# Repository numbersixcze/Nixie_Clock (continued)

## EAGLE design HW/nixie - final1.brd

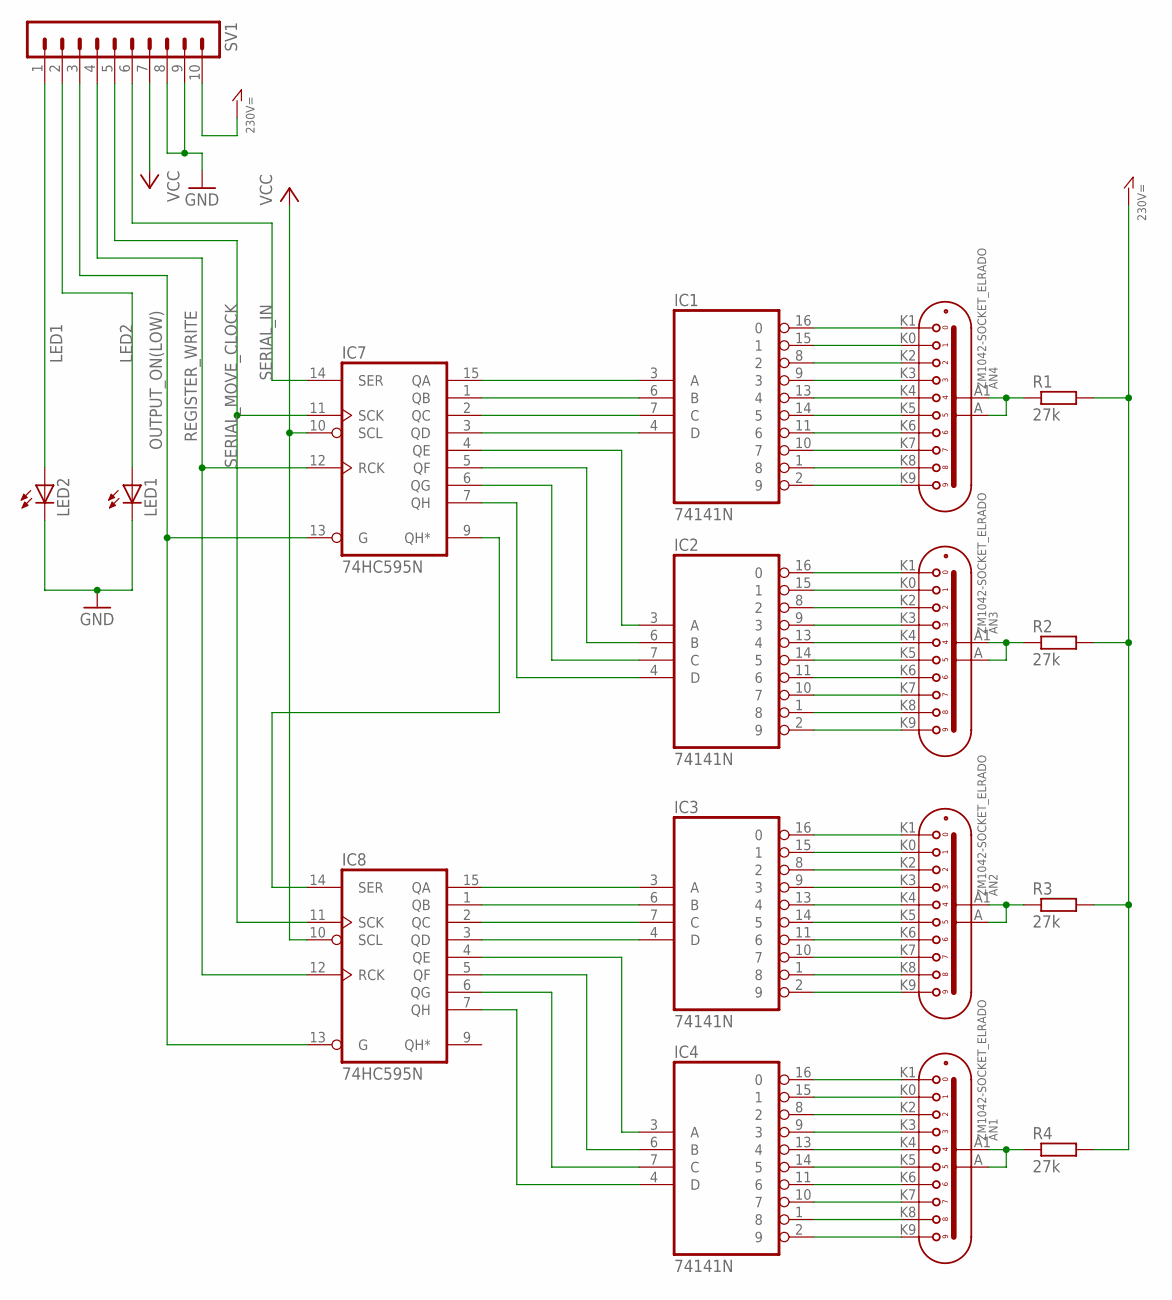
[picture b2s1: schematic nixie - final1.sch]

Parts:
AN1, AN2, AN3, AN4: ZM1042-SOCKET_ELRADO; ZM1040.SOCKET
IC1, IC2, IC3, IC4: 74141N; DIL16
IC7, IC8: 74HC595N; DIL16
LED1, LED2: LED_ELD260; LED_LD260
R1, R2, R3, R4: 27k; 0309/12
SV1: MA10-1

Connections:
230V=: R1.2, R2.2, R3.2, R4.2, SV1.10
GND: IC1.12 (GND), IC2.12 (GND), IC3.12 (GND), IC4.12 (GND), IC7.8 (GND), IC8.8 (GND), LED1.K (C), LED2.K (C), SV1.8, SV1.9
LED1: LED2.A, SV1.1
LED2: LED1.A, SV1.2
unnamed: AN4.K1 (0), IC1.16 (0)
unnamed: AN4.K0 (1), IC1.15 (1)
unnamed: AN4.K2 (2), IC1.8 (2)
unnamed: AN4.K3 (3), IC1.9 (3)
unnamed: AN4.K4 (4), IC1.13 (4)
unnamed: AN4.K5 (5), IC1.14 (5)
unnamed: AN4.K6 (6), IC1.11 (6)
unnamed: AN4.K7 (7), IC1.10 (7)
unnamed: AN4.K8 (8), IC1.1 (8)
unnamed: AN4.K9 (9), IC1.2 (9)
unnamed: AN1.K0 (1), IC4.15 (1)
unnamed: AN1.K2 (2), IC4.8 (2)
unnamed: AN1.K4 (4), IC4.13 (4)
unnamed: AN1.K3 (3), IC4.9 (3)
unnamed: AN1.K5 (5), IC4.14 (5)
unnamed: AN1.K6 (6), IC4.11 (6)
unnamed: AN1.K7 (7), IC4.10 (7)
unnamed: AN1.K8 (8), IC4.1 (8)
unnamed: AN1.K9 (9), IC4.2 (9)
unnamed: AN1.K1 (0), IC4.16 (0)
unnamed: AN2.K0 (1), IC3.15 (1)
unnamed: AN2.K2 (2), IC3.8 (2)
unnamed: AN2.K4 (4), IC3.13 (4)
unnamed: AN2.K3 (3), IC3.9 (3)
unnamed: AN2.K5 (5), IC3.14 (5)
unnamed: AN2.K6 (6), IC3.11 (6)
unnamed: AN2.K7 (7), IC3.10 (7)
unnamed: AN2.K8 (8), IC3.1 (8)
unnamed: AN2.K9 (9), IC3.2 (9)
unnamed: AN2.K1 (0), IC3.16 (0)
unnamed: AN3.K0 (1), IC2.15 (1)
unnamed: AN3.K2 (2), IC2.8 (2)
unnamed: AN3.K4 (4), IC2.13 (4)
unnamed: AN3.K3 (3), IC2.9 (3)
unnamed: AN3.K5 (5), IC2.14 (5)
unnamed: AN3.K6 (6), IC2.11 (6)
unnamed: AN3.K7 (7), IC2.10 (7)
unnamed: AN3.K8 (8), IC2.1 (8)
unnamed: AN3.K9 (9), IC2.2 (9)
unnamed: AN3.K1 (0), IC2.16 (0)
unnamed: IC1.3 (A), IC7.15 (QA)
unnamed: IC1.6 (B), IC7.1 (QB)
unnamed: IC1.7 (C), IC7.2 (QC)
unnamed: IC1.4 (D), IC7.3 (QD)
unnamed: IC2.3 (A), IC7.4 (QE)
unnamed: IC2.6 (B), IC7.5 (QF)
unnamed: IC2.7 (C), IC7.6 (QG)
unnamed: IC2.4 (D), IC7.7 (QH)
unnamed: IC3.3 (A), IC8.15 (QA)
unnamed: IC3.6 (B), IC8.1 (QB)
unnamed: IC3.7 (C), IC8.2 (QC)
unnamed: IC3.4 (D), IC8.3 (QD)
unnamed: IC4.3 (A), IC8.4 (QE)
unnamed: IC4.6 (B), IC8.5 (QF)
unnamed: IC4.7 (C), IC8.6 (QG)
unnamed: IC4.4 (D), IC8.7 (QH)
unnamed: IC7.9 (QH*), IC8.14 (SER)
unnamed: AN4.A (A1), AN4.A1 (A2), R1.1
unnamed: AN3.A (A1), AN3.A1 (A2), R2.1
unnamed: AN2.A (A1), AN2.A1 (A2), R3.1
unnamed: AN1.A (A1), AN1.A1 (A2), R4.1
OUTPUT_ON(LOW): IC7.13 (G), IC8.13 (G), SV1.3
REGISTER_WRITE: IC7.12 (RCK), IC8.12 (RCK), SV1.4
SERIAL_IN: IC7.14 (SER), SV1.6
SERIAL_MOVE_CLOCK: IC7.11 (SCK), IC8.11 (SCK), SV1.5
VCC: IC1.5 (VCC), IC2.5 (VCC), IC3.5 (VCC), IC4.5 (VCC), IC7.10 (SCL), IC7.16 (VCC), IC8.10 (SCL), IC8.16 (VCC), SV1.7

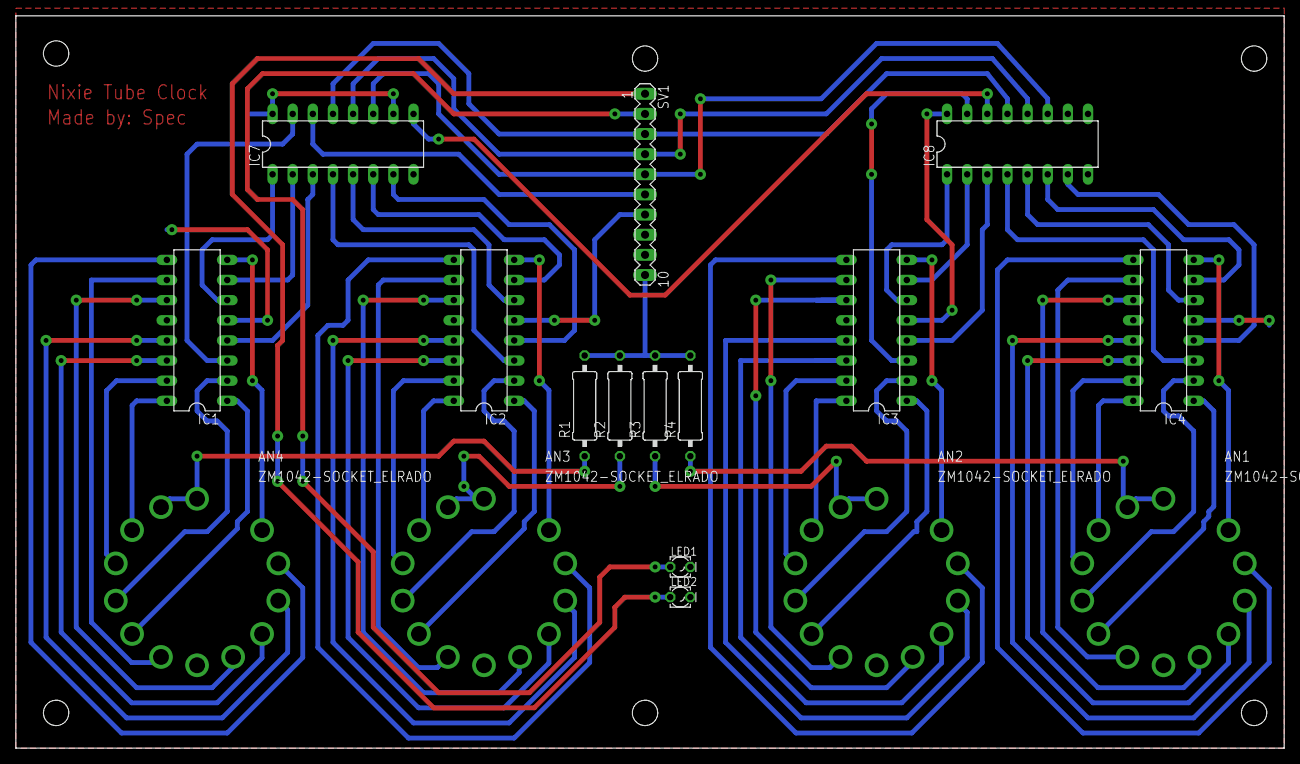
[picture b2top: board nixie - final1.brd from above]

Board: 2 copper layers, 160.0 x 92.4 mm, 17 parts (0 on the bottom side), 70 nets.

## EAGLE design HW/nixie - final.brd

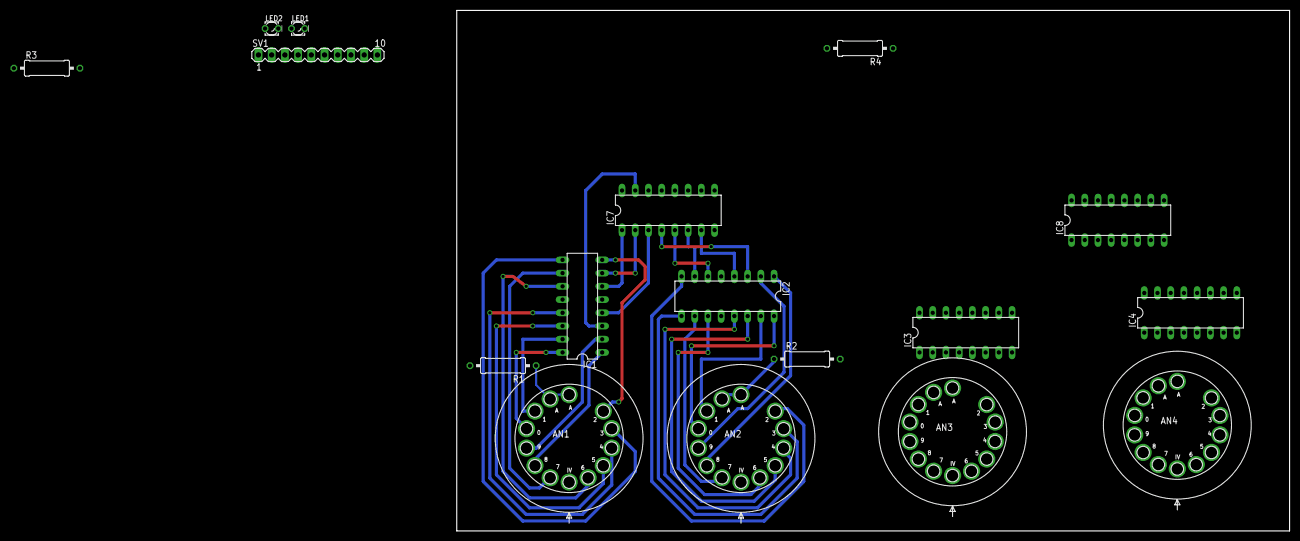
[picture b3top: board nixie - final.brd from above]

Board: 2 copper layers, 160.0 x 100.0 mm, 17 parts (0 on the bottom side), 70 nets.

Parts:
AN1, AN2, AN3, AN4: ZM1042-1-380758-1; ZM1042-AMP
IC1, IC2, IC3, IC4: 74141N; DIL16
IC7, IC8: 74HC595N; DIL16
LED1, LED2: LED_LD260
R1, R2, R3, R4: 27k; 0309/12
SV1: MA10-1

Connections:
230V=: R1.2, R2.2, R3.2, R4.2, SV1.10
GND: IC1.12, IC2.12, IC3.12, IC4.12, IC7.8, IC8.8, LED1.K, LED2.K, SV1.8, SV1.9
LED1: LED2.A, SV1.1
LED2: LED1.A, SV1.2
unnamed: AN1.0, IC1.16
unnamed: AN1.1, IC1.15
unnamed: AN1.2, IC1.8
unnamed: AN1.3, IC1.9
unnamed: AN1.4, IC1.13
unnamed: AN1.5, IC1.14
unnamed: AN1.6, IC1.11
unnamed: AN1.7, IC1.10
unnamed: AN1.8, IC1.1
unnamed: AN1.9, IC1.2
unnamed: AN4.1, IC4.15
unnamed: AN4.2, IC4.8
unnamed: AN4.4, IC4.13
unnamed: AN4.3, IC4.9
unnamed: AN4.5, IC4.14
unnamed: AN4.6, IC4.11
unnamed: AN4.7, IC4.10
unnamed: AN4.8, IC4.1
unnamed: AN4.9, IC4.2
unnamed: AN4.0, IC4.16
unnamed: AN3.1, IC3.15
unnamed: AN3.2, IC3.8
unnamed: AN3.4, IC3.13
unnamed: AN3.3, IC3.9
unnamed: AN3.5, IC3.14
unnamed: AN3.6, IC3.11
unnamed: AN3.7, IC3.10
unnamed: AN3.8, IC3.1
unnamed: AN3.9, IC3.2
unnamed: AN3.0, IC3.16
unnamed: AN2.1, IC2.15
unnamed: AN2.2, IC2.8
unnamed: AN2.4, IC2.13
unnamed: AN2.3, IC2.9
unnamed: AN2.5, IC2.14
unnamed: AN2.6, IC2.11
unnamed: AN2.7, IC2.10
unnamed: AN2.8, IC2.1
unnamed: AN2.9, IC2.2
unnamed: AN2.0, IC2.16
unnamed: IC1.3, IC7.15
unnamed: IC1.6, IC7.1
unnamed: IC1.7, IC7.2
unnamed: IC1.4, IC7.3
unnamed: IC2.3, IC7.4
unnamed: IC2.6, IC7.5
unnamed: IC2.7, IC7.6
unnamed: IC2.4, IC7.7
unnamed: IC3.3, IC8.15
unnamed: IC3.6, IC8.1
unnamed: IC3.7, IC8.2
unnamed: IC3.4, IC8.3
unnamed: IC4.3, IC8.4
unnamed: IC4.6, IC8.5
unnamed: IC4.7, IC8.6
unnamed: IC4.4, IC8.7
unnamed: IC7.9, IC8.14
unnamed: AN1.A, AN1.A1, R1.1
unnamed: AN2.A, AN2.A1, R2.1
unnamed: AN3.A, AN3.A1, R3.1
unnamed: AN4.A, AN4.A1, R4.1
OUTPUT_ON(LOW): IC7.13, IC8.13, SV1.3
REGISTER_WRITE: IC7.12, IC8.12, SV1.4
SERIAL_IN: IC7.14, SV1.6
SERIAL_MOVE_CLOCK: IC7.11, IC8.11, SV1.5
VCC: IC1.5, IC2.5, IC3.5, IC4.5, IC7.10, IC7.16, IC8.10, IC8.16, SV1.7

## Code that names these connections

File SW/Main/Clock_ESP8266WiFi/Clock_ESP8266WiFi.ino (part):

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
// Pin Definition
const uint8_t AnalogPin     = A0;   //analogový vstup z multiplexu
const uint8_t VN_EN_Pin     = 14;   //VN enable  
const uint8_t VN_CTRL_Pin   = 12;   //VN level control
const uint8_t ExtServoPin   = 16;   //Extern Servo Control Pin
const uint8_t SCK_EIO_Pin   = 13;   //SCK to 595 to extended Outputs 
const uint8_t RCK_EIO_Pin   = 15;   //RCK to 595 to extended Outputs
const uint8_t SER_EIO_Pin   = 5;    //serial_in to 595 to extended Outputs
const uint8_t SER_NX_Pin    = 4;    //serial_in to 595 to nixie tubes
const uint8_t SCK_NX_Pin    = 0;    //SCK to 595 to nixie tubes
const uint8_t RCK_NX_Pin    = 2;    //RCK to 595 to nixie tubes

//Loop Times Setup
const uint16_t FastLoopMs = 200;     //Fast loop called thru timer interrupt every x ms
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
//Instance creation
Ticker Timer;                                                           //Create instance of Timer
ShiftRegister74HC595 EIO595(1, SER_EIO_Pin, SCK_EIO_Pin, RCK_EIO_Pin);  //Create instance of shift registr for extended output
ShiftRegister74HC595 NX595(2, SER_NX_Pin, SCK_NX_Pin, RCK_NX_Pin);      //Create instance of shift registr for displaying numbers on nixies

//HEADERS
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{
    //Setting all I/O configs
  pinMode(AnalogPin, INPUT);
  pinMode(VN_EN_Pin, OUTPUT);
  pinMode(VN_CTRL_Pin, OUTPUT);
  pinMode(ExtServoPin, OUTPUT);
  pinMode(SCK_EIO_Pin, OUTPUT);
  pinMode(RCK_EIO_Pin, OUTPUT);
  pinMode(SER_EIO_Pin, OUTPUT);
  pinMode(SCK_NX_Pin, OUTPUT);
  pinMode(RCK_NX_Pin, OUTPUT);
  pinMode(SER_NX_Pin, OUTPUT);
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
void VnOn()
{
  digitalWrite(VN_EN_Pin, 1);
}

void VnOff()
{
  digitalWrite(VN_EN_Pin, 0);
}

void ClockDots(char Dots)
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
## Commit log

2019-03-28 Prvni commit
2019-03-28 Hello_word pokus
2019-03-28 Prubezna dokumentace
2019-03-28 Example
2019-03-28 Example_cele ESP8266 clock s OLED displayem
2019-03-30 Pokus o synchronizaci Desek
2019-04-01 Update dokumentace
2019-04-08 Knihovna pro mDNS
2019-04-08 Prace s http serverem.
2019-04-08 uprava sch
2019-04-11 Update odkazu
2019-04-11 Aktualizace
    pridani knihovny pro hodiny a exmample pro vypis hodin
2019-04-11 Update SCH+BRD
2019-04-11 Modifikace casu. Priklad
2019-04-14 Nova verze pro server
2019-04-21 Pokrok ve schematu
2019-04-23 Pripraveny NTP server pro komunikaci
2019-04-23 Update Hesla
2019-04-23 Kombinace HTTP a NTP
2019-04-24 Rozšířené webové rozhraní
2019-04-25 Pridane rozhrani pro budik a casovac
2019-04-25 Update času a drobné opravy.
2019-04-27 Změna polohy Mainu
2019-04-27 Pridana ochrana pro Parsovani a validni data pro budik
2019-04-27 Osetrene ochrany i pro nastaveni casu. Neukazuje stale.
2019-04-27 Drobné změny s texty
2019-04-28 Example EEPROM
2019-04-28 Drobne zmeny.
2019-04-28 Heslo a ucet do stringu
    syncNTP jako konstanta
2019-04-28 Doplěna změna hesla a loginu
2019-04-28 Přidaná změna hesla pro WIFi, stále nefunkční změna pro NTP
2019-04-28 Uprava NTP do string formatu
2019-04-28 Rozběhaná změna NTP serveru
2019-04-28 Time zony pro NTP
2019-04-28 Upravene formulare
2019-04-28 Použité knihovny
2019-04-28 Postupný postup, SCHEME DON, BRD ALMOST
2019-05-02 Refresh stránek pro budíček. Funguje
2019-05-02 Aktualizace mainu a moznost odhlaseni.
2019-05-02 Pocesteny ikony + overeni zabezpeceni
2019-05-09 Aktualizace aktuální verze desky , nákup a pod.
2019-05-09 Drobná změna chybové stranky.
2019-05-10 Dokumentace v1
2019-05-11 Doplnění ruční IP adresy
2019-05-11 Drobné úpravy s odkazy.
2019-05-16 desky :p
2019-05-18 !Pozor! změna mainu, může být problém
    Přidání Dokumentace.docx
2019-05-20 Přidán mDNS
2019-05-20 Přidání ochrany heslem, drobné úpravy popisků
2019-05-20 Drobne zmeny - odsazeni
2019-05-22 Drobné změny v kódu + dokumentace
2019-05-22 Drobné textové úpravy. Posunutí mDNS. Lepší ošetření SetAlarm pro neplatné znaky.
2019-05-22 Drobná změna v textu
2019-05-22 Pridani off/on digitron
2019-05-22 Update HW, SW - hlavne SW blizke HW, hodiny funkcni, bezi testovaci sekvence, na zmacknuti tlacitka se zobrazi
2019-05-22 Aktualizace dokumentace
2019-05-23 Spojeni s Martinovím kódem, oprava pádu u NTP
2019-05-23 schemata, deska
2019-05-23 Přesunutí tělíček - testováno
2019-05-23 Dokumentace
2019-05-23 Předposlední verze
2019-11-02 Bump lodash in /SW/Examples/NTP+HTTP+HTML/ReStatic-master
    Bumps [lodash](https://github.com/lodash/lodash) from 4.17.11 to 4.17.13.
    - [Release notes](https://github.com/lodash/lodash/releases)
    - [Commits](https://github.com/lodash/lodash/compare/4.17.11...4.17.13)
2020-07-16 Bump lodash in /SW/Examples/NTP+HTTP+HTML/ReStatic-master
    Bumps [lodash](https://github.com/lodash/lodash) from 4.17.11 to 4.17.19.
    - [Release notes](https://github.com/lodash/lodash/releases)
    - [Commits](https://github.com/lodash/lodash/compare/4.17.11...4.17.19)
2021-05-08 Bump lodash in /SW/Examples/NTP+HTTP+HTML/ReStatic-master
    Bumps [lodash](https://github.com/lodash/lodash) from 4.17.11 to 4.17.21.
    - [Release notes](https://github.com/lodash/lodash/releases)
    - [Commits](https://github.com/lodash/lodash/compare/4.17.11...4.17.21)
2021-05-25 Bump browserslist in /SW/Examples/NTP+HTTP+HTML/ReStatic-master
    Bumps [browserslist](https://github.com/browserslist/browserslist) from 4.5.5 to 4.16.6.
    - [Release notes](https://github.com/browserslist/browserslist/releases)
    - [Changelog](https://github.com/browserslist/browserslist/blob/main/CHANGELOG.md)
    - [Commits](https://github.com/browserslist/browserslist/compare/4.5.5...4.16.6)
2021-08-10 Bump path-parse in /SW/Examples/NTP+HTTP+HTML/ReStatic-master
    Bumps [path-parse](https://github.com/jbgutierrez/path-parse) from 1.0.6 to 1.0.7.
    - [Release notes](https://github.com/jbgutierrez/path-parse/releases)
    - [Commits](https://github.com/jbgutierrez/path-parse/commits/v1.0.7)
    ---
    updated-dependencies:
    - dependency-name: path-parse
2023-01-03 Bump json5 in /SW/Examples/NTP+HTTP+HTML/ReStatic-master
    Bumps [json5](https://github.com/json5/json5) from 2.1.0 to 2.2.3.
    - [Release notes](https://github.com/json5/json5/releases)
    - [Changelog](https://github.com/json5/json5/blob/main/CHANGELOG.md)
    - [Commits](https://github.com/json5/json5/compare/v2.1.0...v2.2.3)
    ---
    updated-dependencies:
